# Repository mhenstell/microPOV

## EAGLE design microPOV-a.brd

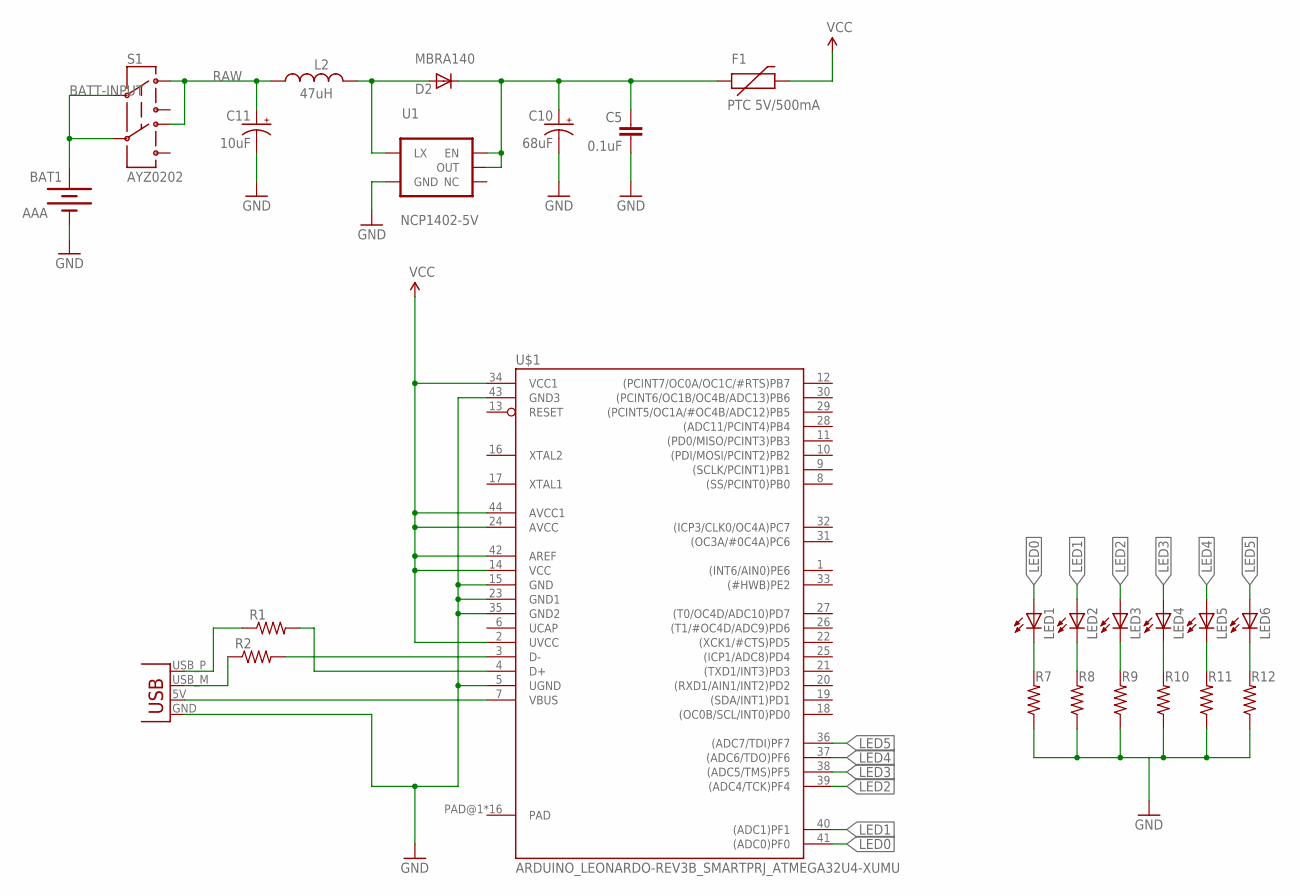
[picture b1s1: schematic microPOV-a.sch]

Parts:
BAT1: AAA; BATTERY-AAA
C5: 0.1uF; 0603-CAP
C10: 68uF; EIA3528-21
C11: 10uF; CPOL_1206
D2: MBRA140; SMA-DIODE
F1: PTC 5V/500mA; PTC-1206
JP1: USBPCB; USB-A-PCB
L2: 47uH; CR54
LED1, LED2, LED3, LED4, LED5, LED6: LEDCHIPLED_1206; CHIPLED_1206
R1, R2, R7, R8, R9, R10, R11, R12: RESISTOR0402-RES; 0402-RES
S1: AYZ0202
U1: NCP1402-5V; SOT23-5
U$1: ARDUINO_LEONARDO-REV3B_SMARTPRJ_ATMEGA32U4-XUMU; ARDUINO_LEONARDO-REV3B_SMARTPRJ_QFN44ML7X7

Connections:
BATT-INPUT: BAT1.PWR@1 (+), S1.2, S1.5
GND: BAT1.GND@1 (-), C5.2, C10.C (-), C11.C (-), JP1.GND, R7.1, R8.1, R9.1, R10.1, R11.1, R12.1, U1.4 (GND), U$1.5 (UGND), U$1.15 (GND), U$1.23 (GND1), U$1.35 (GND2), U$1.43 (GND3)
LED0: LED1.A, U$1.41 ((ADC0)PF0)
LED1: LED2.A, U$1.40 ((ADC1)PF1)
LED2: LED3.A, U$1.39 ((ADC4/TCK)PF4)
LED3: LED4.A, U$1.38 ((ADC5/TMS)PF5)
LED4: LED5.A, U$1.37 ((ADC6/TDO)PF6)
LED5: LED6.A, U$1.36 ((ADC7/TDI)PF7)
unnamed: JP1.5V (VBUS), U$1.7 (VBUS)
unnamed: C5.1, C10.A (+), D2.C, F1.1, U1.1 (EN), U1.2 (OUT)
unnamed: JP1.USB_P (D+), R1.1
unnamed: R1.2, U$1.4 (D+)
unnamed: JP1.USB_M (D-), R2.1
unnamed: R2.2, U$1.3 (D-)
unnamed: LED1.C, R7.2
unnamed: LED2.C, R8.2
unnamed: LED3.C, R9.2
unnamed: LED4.C, R10.2
unnamed: LED5.C, R11.2
unnamed: LED6.C, R12.2
unnamed: D2.A, L2.P$1 (1), U1.5 (LX)
PAD: U$1.PAD@1 (PAD), U$1.PAD@2 (PAD), U$1.PAD@3 (PAD), U$1.PAD@4 (PAD), U$1.PAD@5 (PAD), U$1.PAD@6 (PAD), U$1.PAD@7 (PAD), U$1.PAD@8 (PAD), U$1.PAD@9 (PAD), U$1.PAD@10 (PAD), U$1.PAD@11 (PAD), U$1.PAD@12 (PAD), U$1.PAD@13 (PAD), U$1.PAD@14 (PAD), U$1.PAD@15 (PAD), U$1.PAD@16 (PAD)
RAW: C11.A (+), L2.P$2 (2), S1.3 (1), S1.6 (4)
VCC: F1.2, U$1.2 (UVCC), U$1.14 (VCC), U$1.24 (AVCC), U$1.34 (VCC1), U$1.42 (AREF), U$1.44 (AVCC1)

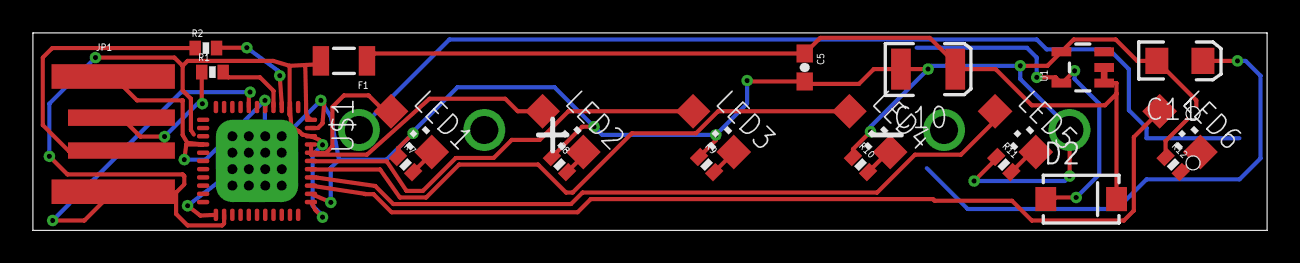
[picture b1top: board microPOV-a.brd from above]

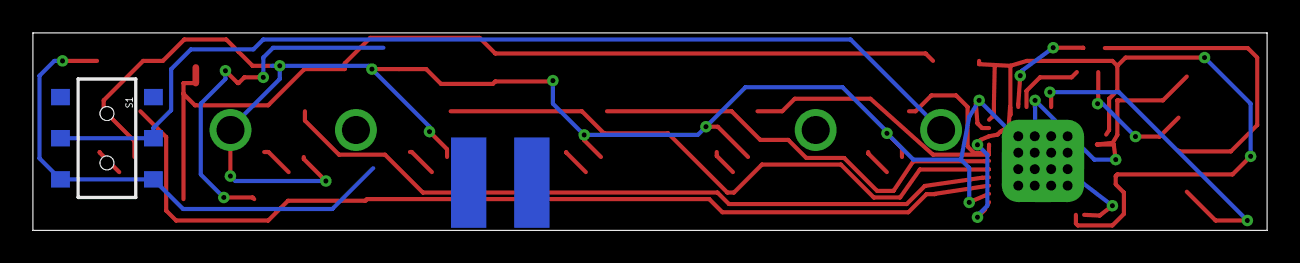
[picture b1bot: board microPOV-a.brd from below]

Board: 2 copper layers, 75.0 x 12.0 mm, 25 parts (2 on the bottom side), 24 nets.

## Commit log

2013-03-09 initial

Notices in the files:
parts and their libraries:
SparkFun-Connectors: Licensing: CC v3.0 Share-Alike You are welcome to use this library for commercial purposes.
